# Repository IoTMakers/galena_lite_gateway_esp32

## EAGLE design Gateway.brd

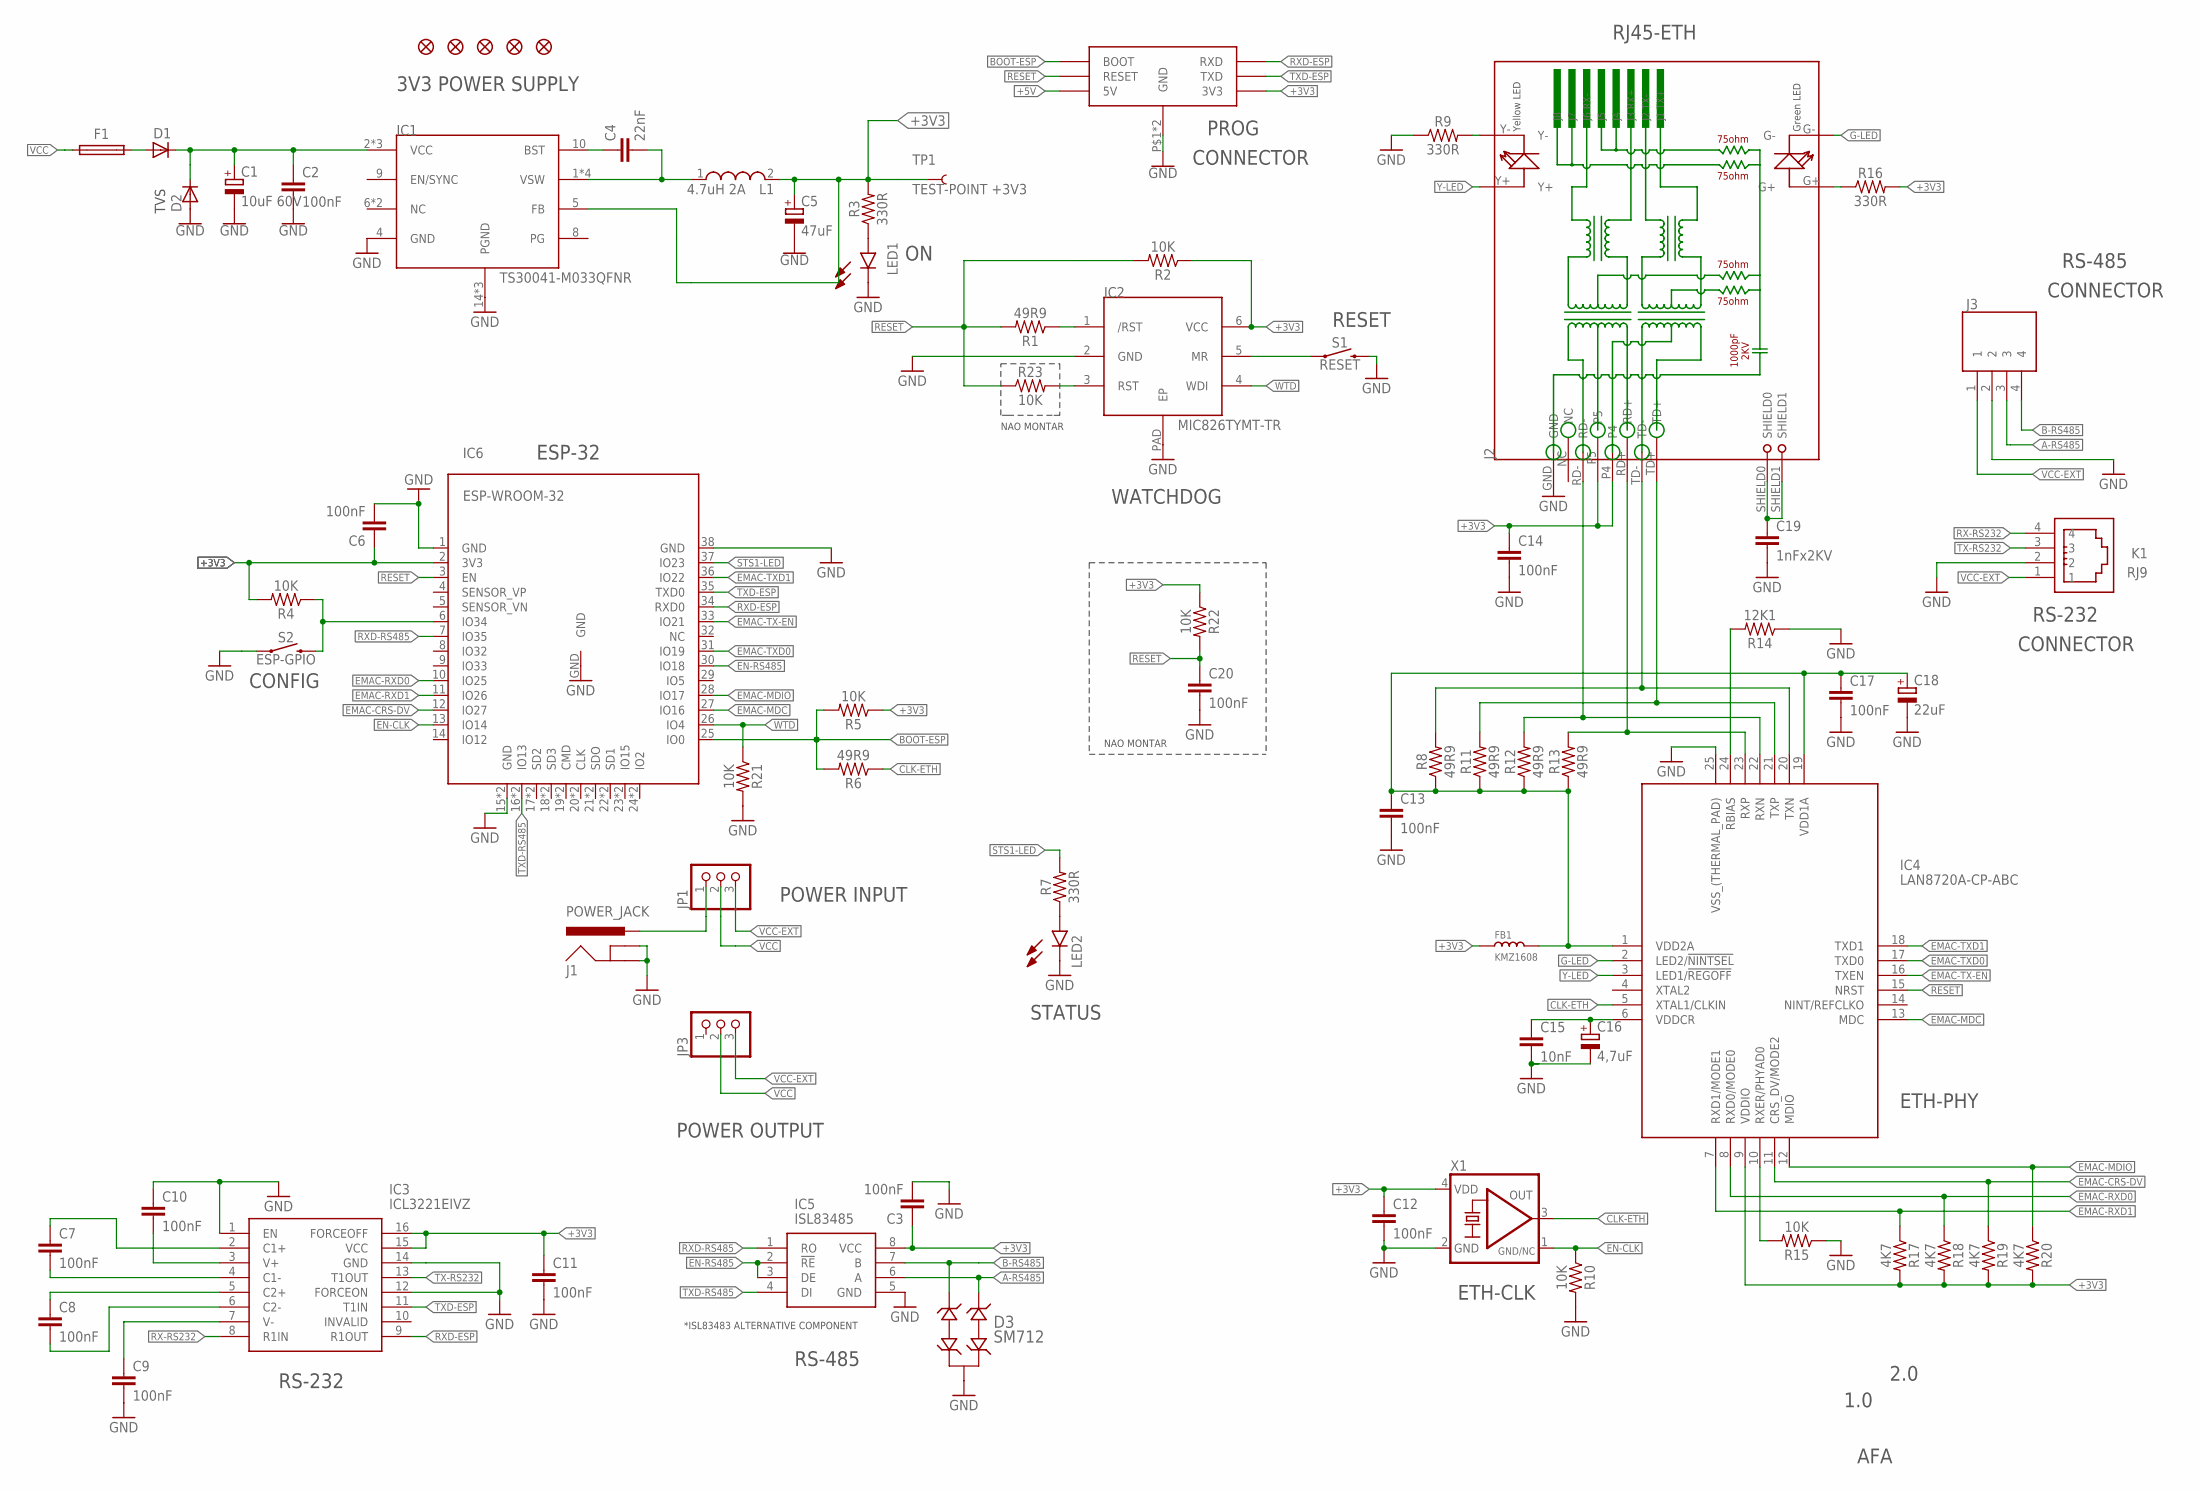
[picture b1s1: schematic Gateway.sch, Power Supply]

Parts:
C1: 10uF 60V; UD-6,3X7,7_NICHICON
C2, C3, C6, C7, C8, C9, C10, C11, C12, C13, C14, C17, C20: 100nF; 0603
C4: 22nF; 0603
C5: 47uF; UD-6,3X7,7_NICHICON
C15: 10nF; 0603
C16: 4,7uF; UD-6,3X7,7_NICHICON
C18: 22uF; UD-6,3X7,7_NICHICON
C19: 1nFx2KV; 1206
D1, D2: DIODE-SMB; SMB
D3: SM712; SOT-23-3
F1: FUSE_0679L
FB1: KMZ1608; L0603
FD1, FD2, FD3, FD4, FD5: FIDUCIAL1X2; FIDUCIAL-1X2
IC1: TS30041-M033QFNR; QFN50P300X300X100-17N
IC2: MIC826TYMT-TR; DFN-6
IC3: ICL3221EIVZ; SOP65P640X120-16N
IC4: LAN8720A-CP-ABC; QFN50P400X400X100-25N
IC5: ISL83485; SOIC127P600X175-8N
IC6: ESP-WROOM-32
J1: POWER_JACK; POWER_JACK_PTH
J2: RJ45-HR911105A-HR911105A; RJ45
J3: 1757268; SHDR4W120P0X508_1X4_2224X1200X
JP1, JP3: PINHD-1X3; 1X03
K1: RJ9; 615004143821
L1: 4.7uH 2A; INDM4949X200N
LED1, LED2: LTST-S220GKT; LTST-S220KFKT
R1, R6, R8, R11, R12, R13: 49R9; 0603
R2, R4, R5, R10, R15, R21, R22, R23: 10K; 0603
R3, R7, R9, R16: 330R; 0603
R14: 12K1; 0603
R17, R18, R19, R20: 4K7; 0603
S1: RESET; TACTILE_SWITCH_PTH_RIGHT_ANGLE_KIT
S2: ESP-GPIO; TACTILE_SWITCH_PTH_RIGHT_ANGLE_KIT
TP1: TEST-POINT +3V3; PAD.03X.05
U$4: ESP-PROGESPROG-4; ESPROG-4
X1: KXO-TCXO-CMOS-82; 7.0X5.0_KXO-82-TCXO

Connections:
+3V3: C3.1, C5.+, C6.1, C11.1, C12.1, C14.1, FB1.1, IC1.5 (FB), IC2.6 (VCC), IC3.15 (VCC), IC3.16 (FORCEOFF), IC4.9 (VDDIO), IC5.8 (VCC), IC6.2 (3V3), J2.P4, J2.P5, L1.2, R2.1, R3.2, R4.2, R5.1, R16.2, R17.2, R18.2, R19.2, R20.2, R22.1, TP1.P$1, U$4.3V3, X1.4 (VDD)
+5V: U$4.5V0 (5V)
A-RS485: D3.2 (IO2), IC5.6 (A), J3.3
B-RS485: D3.1 (IO1), IC5.7 (B), J3.4
BOOT-ESP: IC6.25 (IO0), R5.2, R6.2, U$4.BOOT
CLK-ETH: IC4.5 (XTAL1/CLKIN), R6.1, X1.3 (OUT)
EMAC-CRS-DV: IC4.11 (CRS_DV/MODE2), IC6.12 (IO27), R19.1
EMAC-MDC: IC4.13 (MDC), IC6.27 (IO16)
EMAC-MDIO: IC4.12 (MDIO), IC6.28 (IO17), R20.1
EMAC-RXD0: IC4.8 (RXD0/MODE0), IC6.10 (IO25), R18.1
EMAC-RXD1: IC4.7 (RXD1/MODE1), IC6.11 (IO26), R17.1
EMAC-TX-EN: IC4.16 (TXEN), IC6.33 (IO21)
EMAC-TXD0: IC4.17 (TXD0), IC6.31 (IO19)
EMAC-TXD1: IC4.18 (TXD1), IC6.36 (IO22)
EN-CLK: IC6.13 (IO14), R10.1, X1.1 (GND/NC)
EN-RS485: IC5.2 (!RE), IC5.3 (DE), IC6.30 (IO18)
G-LED: IC4.2 (LED2/!NINTSEL), J2.G-
GND: C1.-, C2.2, C3.2, C5.-, C6.2, C9.2, C10.1, C11.2, C12.2, C13.2, C14.2, C15.2, C16.-, C17.2, C18.-, C19.2, C20.2, D2.A, D3.3 (GND), IC1.4 (GND), IC1.14 (PGND), IC1.15 (PGND), IC1.17 (PGND), IC2.2 (GND), IC2.PAD (EP), IC3.1 (EN), IC3.12 (FORCEON), IC3.14 (GND), IC4.25 (VSS_(THERMAL_PAD)), IC5.5 (GND), IC6.1 (GND), IC6.15 (GND), IC6.38 (GND), IC6.39 (GND), IC6.GND, J1.GND, J1.GNDBREAK, J2.GND, J3.2, K1.2, LED1.2 (K), LED2.2 (K), R9.1, R10.2, R14.1, R15.1, R21.2, S1.2, S2.1, U$4.P$1 (GND), U$4.P$8 (GND), X1.2 (GND)
unnamed: IC2.5 (MR), S1.1
unnamed: C7.1, IC3.2 (C1+)
unnamed: C7.2, IC3.4 (C1-)
unnamed: IC6.6 (IO34), R4.1, S2.2
unnamed: C8.1, IC3.5 (C2+)
unnamed: D1.A, F1.1
unnamed: C8.2, IC3.6 (C2-)
unnamed: C10.2, IC3.3 (V+)
unnamed: C9.1, IC3.7 (V-)
unnamed: J1.PWR, JP1.1
unnamed: LED1.1 (A), R3.1
unnamed: C4.1, IC1.10 (BST)
unnamed: C13.1, C17.1, C18.+, FB1.2, IC4.1 (VDD2A), IC4.19 (VDD1A), R8.1, R11.1, R12.1, R13.1
unnamed: C19.1, J2.SHIELD0, J2.SHIELD1
unnamed: IC2.3 (RST), R23.2
unnamed: IC2.1 (/RST), R1.1
unnamed: C4.2, IC1.1 (VSW), IC1.12 (VSW), IC1.13 (VSW), IC1.16 (VSW), L1.1
unnamed: LED2.1 (A), R7.1
unnamed: J2.G+, R16.1
unnamed: IC4.23 (RXP), J2.RD+, R13.2
unnamed: IC4.22 (RXN), J2.RD-, R12.2
unnamed: IC4.21 (TXP), J2.TD+, R11.2
unnamed: J2.Y-, R9.2
unnamed: IC4.20 (TXN), J2.TD-, R8.2
unnamed: C15.1, C16.+, IC4.6 (VDDCR)
unnamed: IC4.24 (RBIAS), R14.2
unnamed: IC4.10 (RXER/PHYAD0), R15.2
POWER: C1.+, C2.1, D1.C, D2.C, IC1.2 (VCC), IC1.3 (VCC), IC1.11 (VCC)
RESET: C20.1, IC4.15 (NRST), IC6.3 (EN), R1.2, R2.2, R22.2, R23.1, U$4.RESET
RX-RS232: IC3.8 (R1IN), K1.4
RXD-ESP: IC3.9 (R1OUT), IC6.34 (RXD0), U$4.RXD
RXD-RS485: IC5.1 (RO), IC6.7 (IO35)
STS1-LED: IC6.37 (IO23), R7.2
TX-RS232: IC3.13 (T1OUT), K1.3
TXD-ESP: IC3.11 (T1IN), IC6.35 (TXD0), U$4.TXD
TXD-RS485: IC5.4 (DI), IC6.16 (IO13), IC6.40 (IO13)
VCC: F1.2, JP1.2, JP3.2
VCC-EXT: J3.1, JP1.3, JP3.3, K1.1
WTD: IC2.4 (WDI), IC6.26 (IO4), R21.1
Y-LED: IC4.3 (LED1/!REGOFF), J2.Y+

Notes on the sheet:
*ISL83483 ALTERNATIVE COMPONENT
RS-232
RS-485
STATUS
POWER OUTPUT
POWER INPUT
ESP-32
ETH-CLK
ETH-PHY
CONNECTOR
RJ45-ETH
WATCHDOG
PROG
3V3 POWER SUPPLY
2.0
1.0
AFA
NAO MONTAR
TVS
RESET
CONFIG

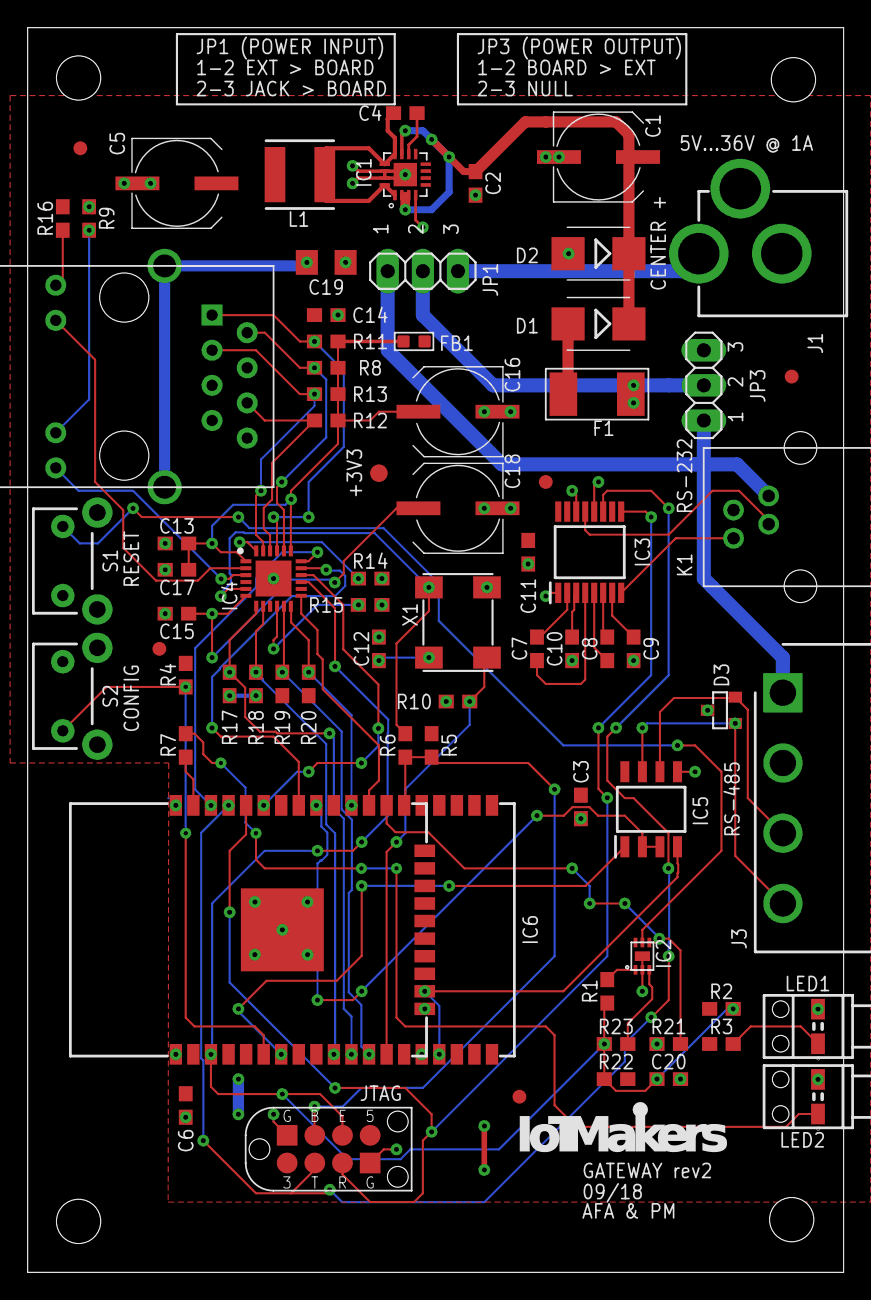
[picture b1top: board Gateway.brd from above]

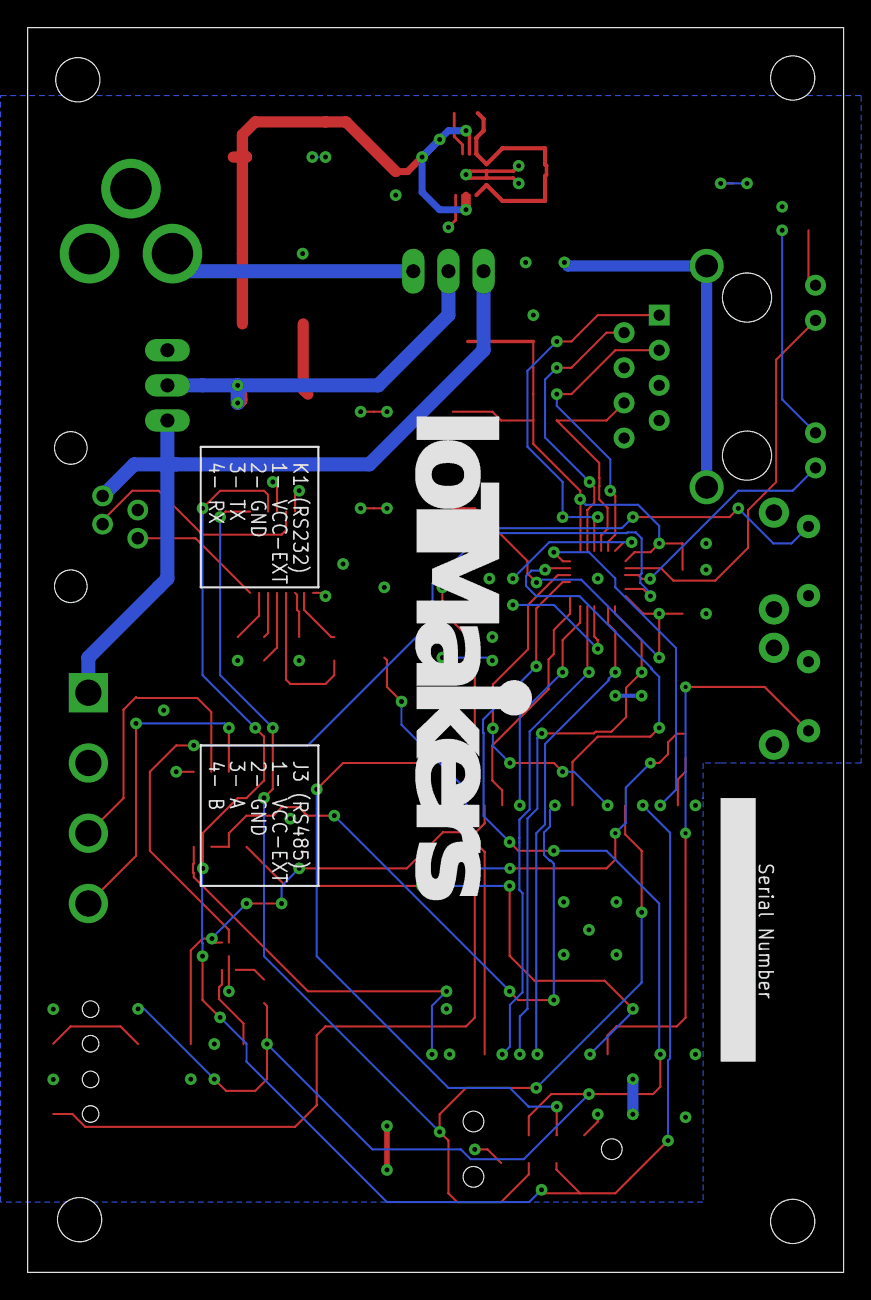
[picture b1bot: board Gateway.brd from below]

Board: 2 copper layers, 59.0 x 90.0 mm, 81 parts (2 on the bottom side), 57 nets.

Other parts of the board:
U$1: LOGO_L
U$2, U$6, U$8, U$9: HOLE-3.2/7.0
U$3: LOGO_XL
U$5, U$7: BIVAR_SLP3-350-100-F

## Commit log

2020-08-04 Files added

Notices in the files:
parts and their libraries:
SparkFun-Resistors: Licensing: Creative Commons ShareAlike 4.0 International - https://creativecommons.org/licenses/by-sa/4.0
crystal-geyer_V1_0: Copyright: Geyer-Electronic
Wurth_Elektronik_Electromechanic_Input-O: Copyright: Würth Elektronik
